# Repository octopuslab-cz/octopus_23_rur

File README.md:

# octopus_23_rur
Retro Ultra Replica of several computers - because we can - ESP32 &amp; Micropython

---

2021 - https://github.com/octopuslab-cz/micropython_4004-emul

2022 - https://github.com/octopuslab-cz/esp32_micropython_uni_digi_interface

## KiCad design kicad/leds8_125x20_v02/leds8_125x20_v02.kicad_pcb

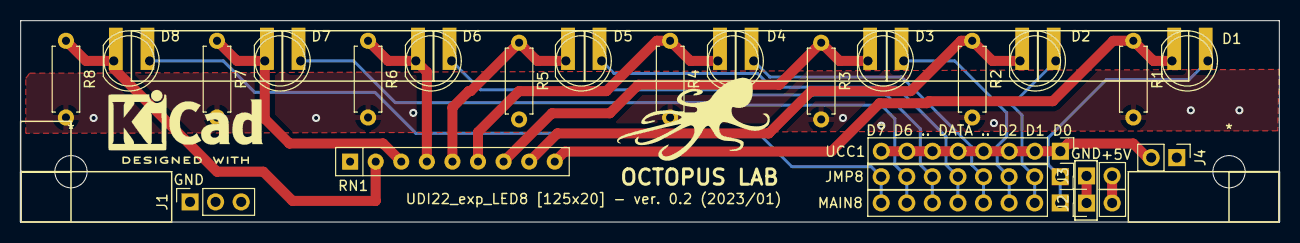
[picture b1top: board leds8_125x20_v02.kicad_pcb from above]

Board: 2 copper layers, 125.0 x 20.0 mm, 28 parts (0 on the bottom side), 14 nets.

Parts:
*: MountingHole_3.2mm_M3
*#2: MountingHole_3.2mm_M3
D1, D2, D3, D4, D5, D6, D7, D8: LED; LED_D5.0mm_OCT
J1: Conn_01x03_Female; PinSocket_1x03_P2.54mm_Vertical
J2, J3: Conn_01x02_Female; PinHeader_1x02_P2.54mm_Vertical
J4: PWR; PinHeader_1x02_P2.54mm_Vertical
JMP8: Conn_01x08_Male; PinHeader_1x08_P2.54mm_Vertical
MAIN8: Conn_01x08_Male; PinHeader_1x08_P2.54mm_Vertical
OCTOPUS LAB: LOGO; symbol16silk_OCTO
R1, R2, R3, R4, R5, R6, R7, R8: R; R_Axial_DIN0207_L6.3mm_D2.5mm_P7.62mm_Horizontal
RN1: R_Network08; R_Array_SIP9
U$2: OCTOPUSLAB
UCC1: Conn_01x08_Male; PinHeader_1x08_P2.54mm_Vertical

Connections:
+5V: J4.2, UCC1.1, UCC1.2, UCC1.3, UCC1.4, UCC1.5, UCC1.6, UCC1.7, UCC1.8
GND: J1.1, J4.1, R1.2, R2.2, R3.2, R4.2, R5.2, R6.2, R7.2, R8.2, RN1.1 (common)
unnamed: D1.2 (A), JMP8.1, MAIN8.1
unnamed: D1.1 (K), D3.1 (K), D5.1 (K), D7.1 (K), R1.1, R3.1, R5.1, R7.1, RN1.3 (R2), RN1.5 (R4), RN1.7 (R6), RN1.9 (R8)
unnamed: D2.2 (A), JMP8.2, MAIN8.2
unnamed: D2.1 (K), D4.1 (K), D6.1 (K), D8.1 (K), R2.1, R4.1, R6.1, R8.1, RN1.2 (R1), RN1.4 (R3), RN1.6 (R5), RN1.8 (R7)
unnamed: D3.2 (A), JMP8.3, MAIN8.3
unnamed: D4.2 (A), JMP8.4, MAIN8.4
unnamed: D5.2 (A), JMP8.5, MAIN8.5
unnamed: D6.2 (A), JMP8.6, MAIN8.6
unnamed: D7.2 (A), JMP8.7, MAIN8.7
unnamed: D8.2 (A), JMP8.8, MAIN8.8
unnamed: J2.1, J3.1
unnamed: J2.2, J3.2

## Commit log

2023-01-31 add kicad project
2023-01-31 typo

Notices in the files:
parts and their libraries:
(c) 2017 - 2019
